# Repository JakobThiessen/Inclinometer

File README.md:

# Inclinometer

- Digital Inclinometer
- Chargetime: 2,5h
- Battery: 250mAh (LiPo)

# Hardware

2 x BMI160

SSD1306

USB --> (VCP) VirtualComPort

# Todo:
## Calibration
## Bootloader over USB

https://github.com/microsoft/uf2

https://github.com/microsoft/uf2-samdx1

# Ab hier nur Beispiel für Markdown-syntax

## Pictures

## Hyperlink

<https://www.markdownguide.org>

<fake@example.com>

<br>

## C++ Example

```cpp
int main() {
  int y = SOME_MACRO_REFERENCE;
  int x = 5 + 6;
  cout << "Hello World! " << x << std::endl();
}
```

## C Example

```c
int main() {
  int y = SOME_MACRO_REFERENCE;
  int x = 5 + 6;
  cout << "Hello World! " << x << std::endl();
}
```

 ## Table
| Column 1      | Column 2     | Column 3     |
| :------------ | :----------- | ------------ |
| Cell Contents | More Stuff   | And Again    |
| You Can Also  | Put Pipes In | Like this \| |

<br>
<br>
<br>

| Column 1   | Column 2   | Column 3                     |
| ---------- | ---------- | ---------------------------- |
| **Things** | _Don't_    | [Need](http://makeuseof.com) |
| To         | *__Look__* | `Pretty`                     |

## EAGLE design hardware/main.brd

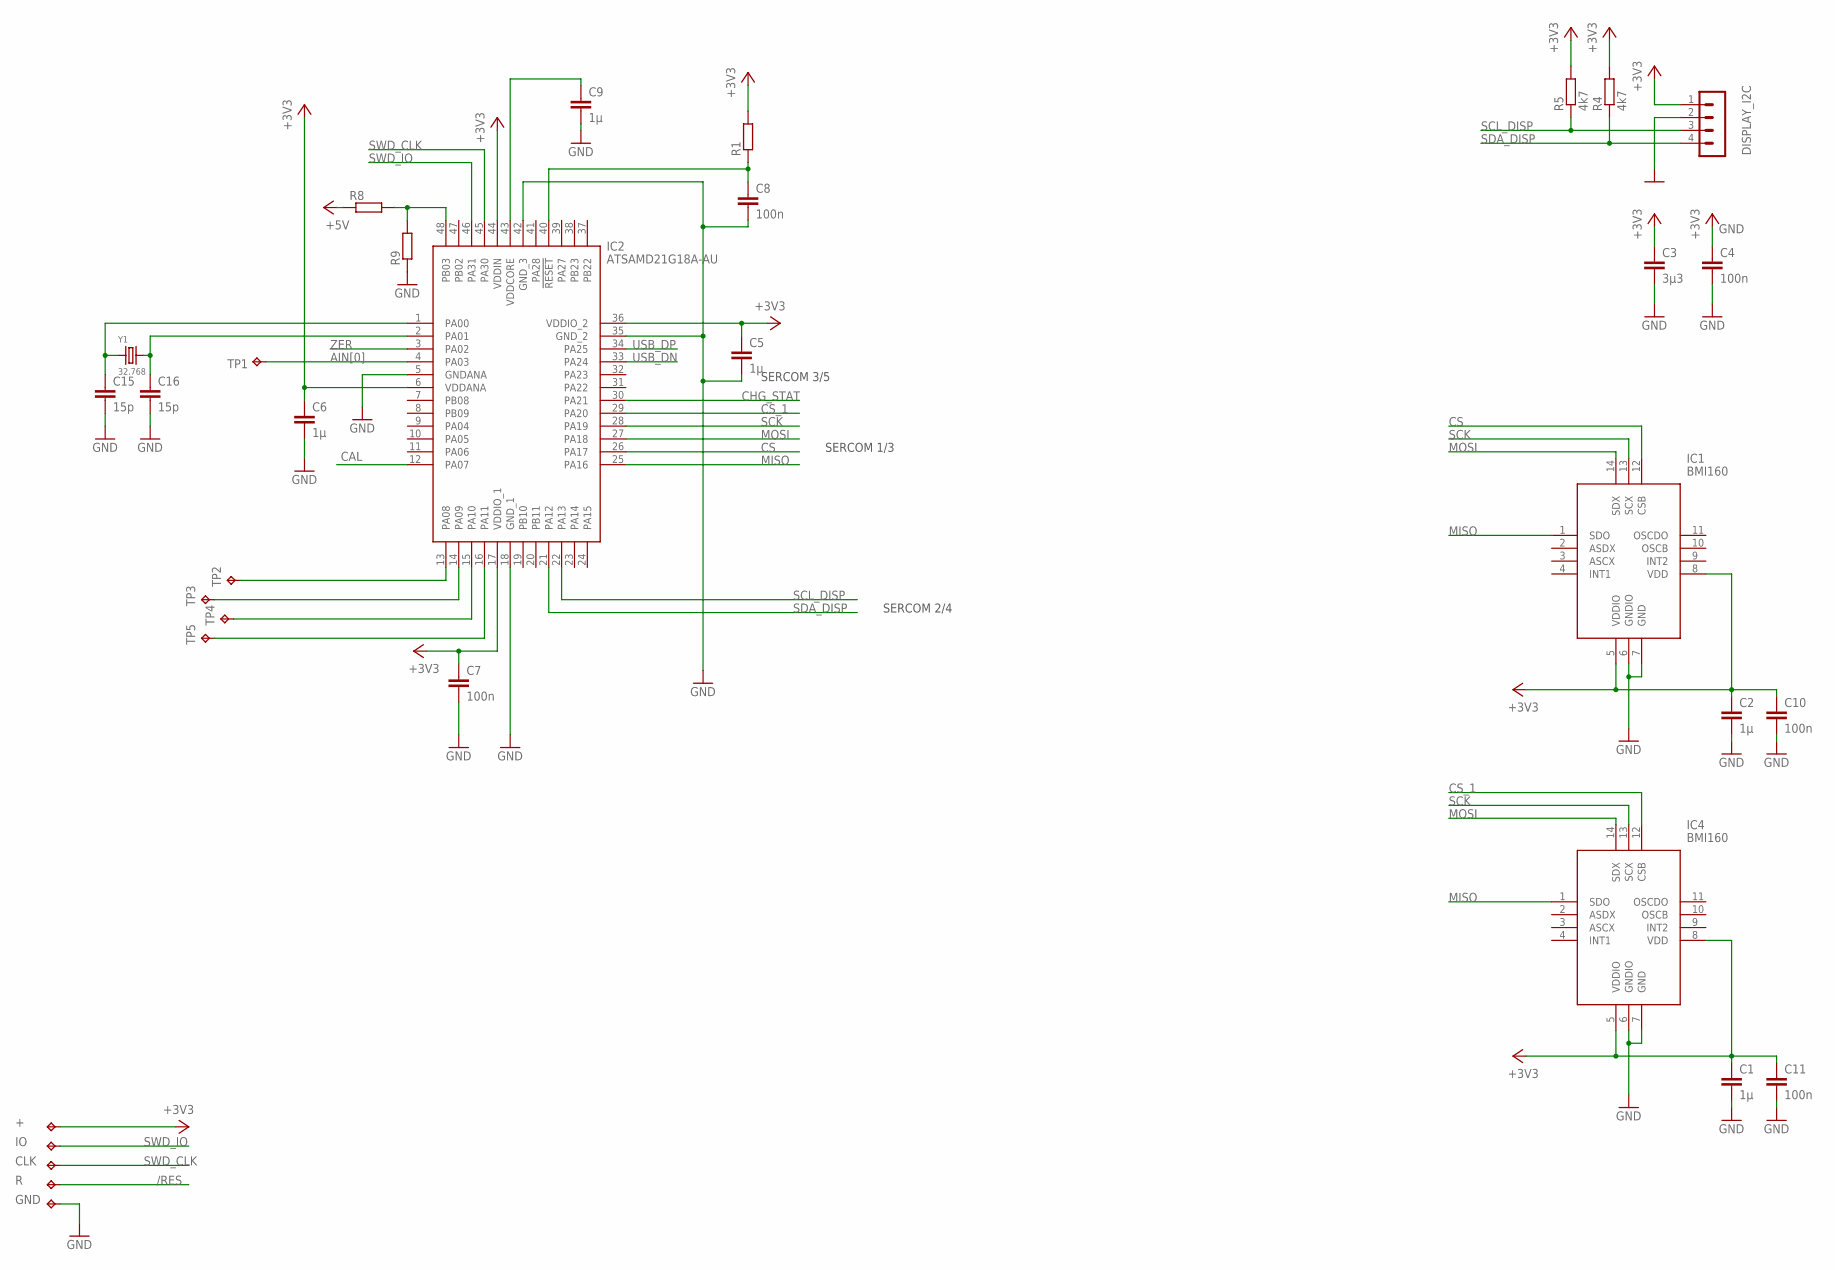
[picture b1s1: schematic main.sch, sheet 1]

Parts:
+: TPB1,27; B1,27
C1, C2, C5, C6, C9: 1µ; C0402K
C3: 3µ3; C0402K
C4, C7, C8, C10, C11: 100n; C0402K
C15, C16: 15p; C0402
CLK: TPB1,27; B1,27
DISPLAY_I2C: MA04-1
GND: TPB1,27; B1,27
IC1, IC4: BMI160; PQFN50P300X250X88-14N
IC2: ATSAMD21G18A-AU; QFP50P900X900X120-48N
IO: TPB1,27; B1,27
R: TPB1,27; B1,27
R1, R8, R9: R-EU_R0402; R0402
R4, R5: 4k7; R0402
TP1, TP2, TP3, TP4, TP5: TPB1,27; B1,27
Y1: 32.768; CRYSTAL_4.9X1.8

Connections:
+3V3: +.TP, C1.1, C2.1, C3.1, C4.1, C5.1, C6.1, C7.1, C10.1, C11.1, DISPLAY_I2C.1, IC1.5 (VDDIO), IC1.8 (VDD), IC2.6 (VDDANA), IC2.17 (VDDIO_1), IC2.36 (VDDIO_2), IC2.44 (VDDIN), IC4.5 (VDDIO), IC4.8 (VDD), R1.2, R4.2, R5.2; also elsewhere on the board
+5V: R8.1; also elsewhere on the board
/RES: C8.1, IC2.40 (!RESET), R.TP, R1.1
AIN[0]: IC2.4 (PA03), TP1.TP
CAL: IC2.12 (PA07); also elsewhere on the board
CHG_STAT: IC2.30 (PA21); also elsewhere on the board
CS: IC1.12 (CSB), IC2.26 (PA17)
CS_1: IC2.29 (PA20), IC4.12 (CSB)
GND: C1.2, C2.2, C3.2, C4.2, C5.2, C6.2, C7.2, C8.2, C9.2, C10.2, C11.2, C15.2, C16.2, DISPLAY_I2C.2, GND.TP, IC1.6 (GNDIO), IC1.7 (GND), IC2.5 (GNDANA), IC2.18 (GND_1), IC2.35 (GND_2), IC2.42 (GND_3), IC4.6 (GNDIO), IC4.7 (GND), R9.1; also elsewhere on the board
MISO: IC1.1 (SDO), IC2.25 (PA16), IC4.1 (SDO)
MOSI: IC1.14 (SDX), IC2.27 (PA18), IC4.14 (SDX)
unnamed: C9.1, IC2.43 (VDDCORE)
unnamed: IC2.13 (PA08), TP2.TP
unnamed: IC2.14 (PA09), TP3.TP
unnamed: IC2.15 (PA10), TP4.TP
unnamed: IC2.16 (PA11), TP5.TP
unnamed: IC2.48 (PB03), R8.2, R9.2
unnamed: C16.1, IC2.2 (PA01), Y1.2
unnamed: C15.1, IC2.1 (PA00), Y1.1
SCK: IC1.13 (SCX), IC2.28 (PA19), IC4.13 (SCX)
SCL_DISP: DISPLAY_I2C.3, IC2.22 (PA13), R5.1
SDA_DISP: DISPLAY_I2C.4, IC2.21 (PA12), R4.1
SWD_CLK: CLK.TP, IC2.45 (PA30)
SWD_IO: IC2.46 (PA31), IO.TP
USB_DN: IC2.33 (PA24); also elsewhere on the board
USB_DP: IC2.34 (PA25); also elsewhere on the board
ZER: IC2.3 (PA02); also elsewhere on the board

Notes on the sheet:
SERCOM 3/5
SERCOM 1/3
SERCOM 2/4

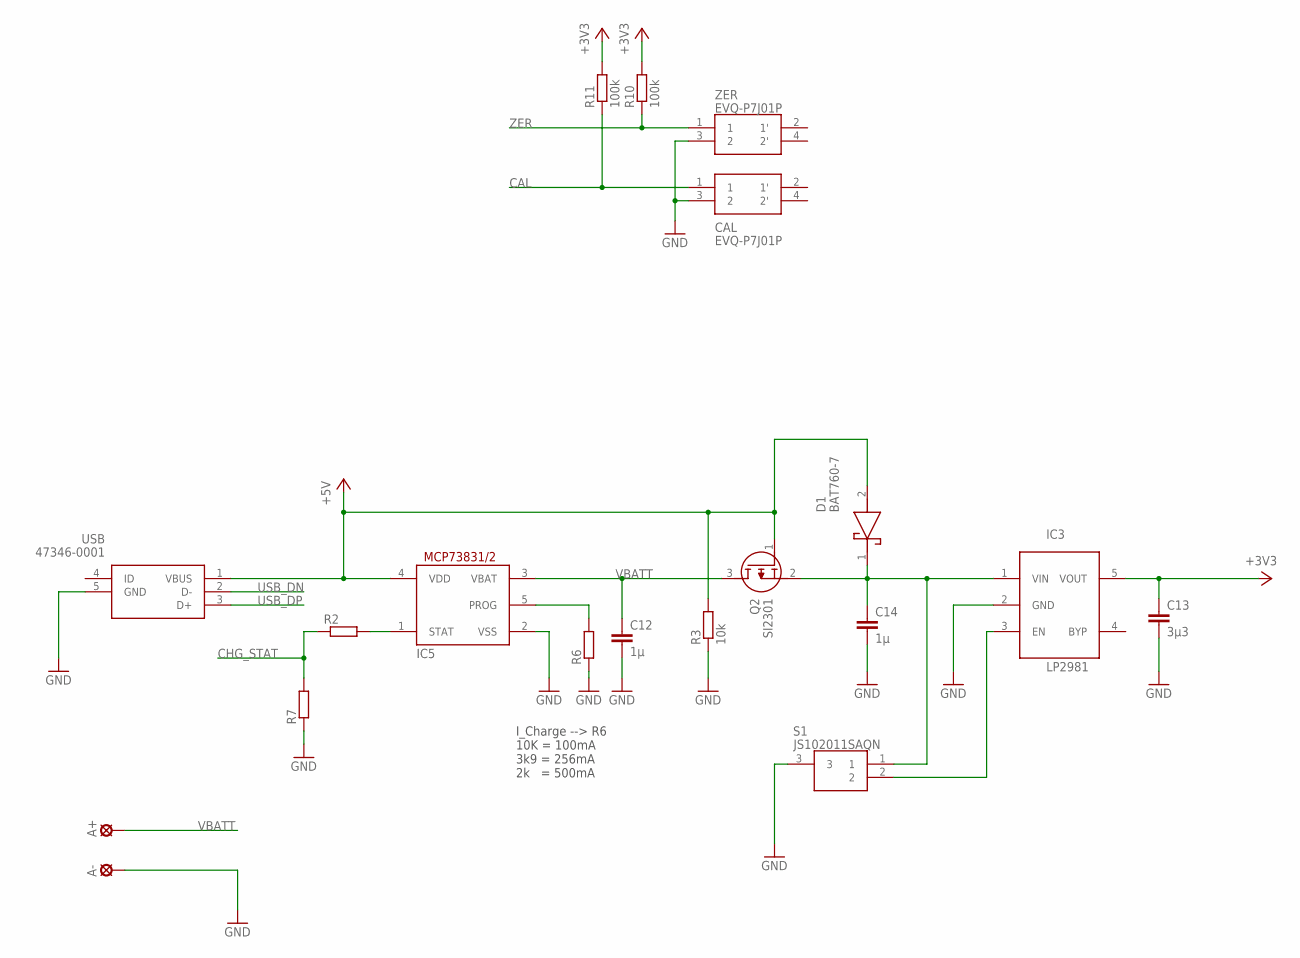
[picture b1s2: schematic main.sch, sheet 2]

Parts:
A+: MCS08
A-: MCS08
C12, C14: 1µ; C0603
C13: 3µ3; C0603
CAL: EVQ-P7J01P; EVQP7J01P
D1: BAT760-7; SOD2513X120N
IC3: LP2981; SOT23-5L
IC5: MCP73831/OT; SOT23-5L
Q2: SI2301; SOT95P240X120-3N
R2, R6, R7: R-EU_R0402; R0402
R3: 10k; R0402
R10, R11: 100k; R0402
S1: JS102011SAQN
USB: 47346-0001
ZER: EVQ-P7J01P; EVQP7J01P

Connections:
+3V3: C13.1, IC3.5 (VOUT), R10.2, R11.2; also elsewhere on the board
+5V: D1.2 (A), IC5.4 (VDD), Q2.1 (G), R3.2, USB.1 (VBUS); also elsewhere on the board
CAL: CAL.1, R11.1; also elsewhere on the board
CHG_STAT: R2.1, R7.2; also elsewhere on the board
GND: A-.MP, C12.2, C13.2, C14.2, CAL.3 (2), IC3.2 (GND), IC5.2 (VSS), R3.1, R6.1, R7.1, S1.3, USB.5 (GND), ZER.3 (2); also elsewhere on the board
unnamed: IC3.3 (EN), S1.2
unnamed: C14.1, D1.1 (K), IC3.1 (VIN), Q2.2 (S), S1.1
unnamed: IC5.1 (STAT), R2.2
unnamed: IC5.5 (PROG), R6.2
USB_DN: USB.2 (D-); also elsewhere on the board
USB_DP: USB.3 (D+); also elsewhere on the board
VBATT: A+.MP, C12.1, IC5.3 (VBAT), Q2.3 (D)
ZER: R10.1, ZER.1; also elsewhere on the board

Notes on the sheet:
I_Charge --> R6 10K = 100mA 3k9 = 256mA 2k = 500mA

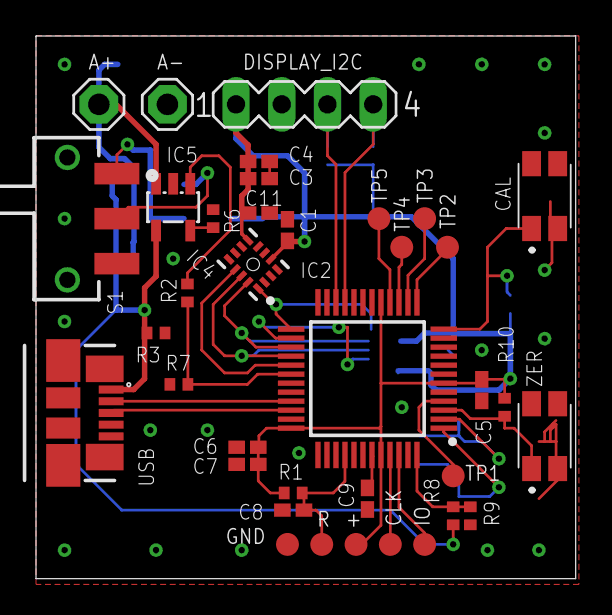
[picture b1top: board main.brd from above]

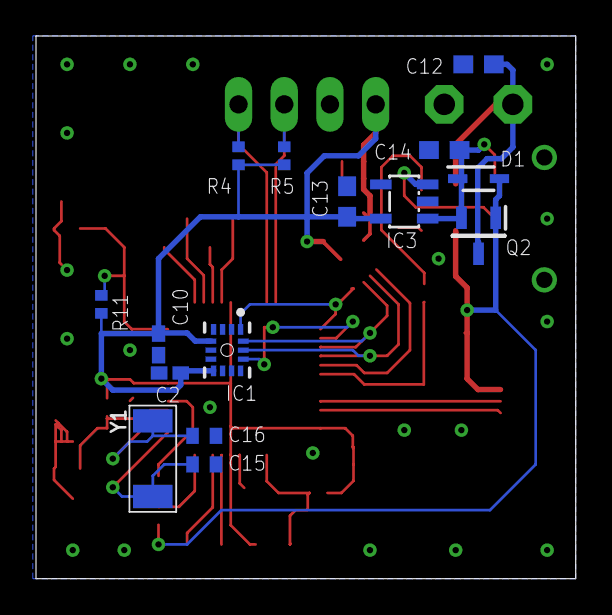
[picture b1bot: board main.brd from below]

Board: 2 copper layers, 30.0 x 30.1 mm, 52 parts (15 on the bottom side), 32 nets.

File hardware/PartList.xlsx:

Qty | vorhanden | Value | Device | Package | Parts | Description | ARROW_PART_NUMBER | ARROW_PRICE-STOCK | HEIGHT | MANUFACTURER_NAME | MANUFACTURER_PART_NUMBER
1 |  |  | MA04-1 | MA04-1 | DISPLAY_I2C | PIN HEADER
6 |  |  | R-EU_R0402 | R0402 | R1, R2, R6, R7, R8, R9 | RESISTOR, European symbol
2 | x | 100k | R-EU_R0402 | R0402 | R10, R11 | RESISTOR, European symbol
5 | x | 100n | C-EUC0402K | C0402K | C4, C7, C8, C10, C11 | CAPACITOR, European symbol
1 | x | 10k | R-EU_R0402 | R0402 | R3 | RESISTOR, European symbol
2 | x | 15p | C-EUC0402 | C0402 | C15, C16 | CAPACITOR, European symbol
5 | x | 1µ | C-EUC0402K | C0402K | C1, C2, C5, C6, C9 | CAPACITOR, European symbol
2 | x | 1µ | C-EUC0603 | C0603 | C12, C14 | CAPACITOR, European symbol
1 | x | 32768 | CRYSTALTHIN32K | CRYSTAL_4.9X1.8 | Y1 | Crystals
1 | x | 3µ3 | C-EUC0402K | C0402K | C3 | CAPACITOR, European symbol
1 | x | 3µ3 | C-EUC0603 | C0603 | C13 | CAPACITOR, European symbol
1 | x | 47346-0001 | 47346-0001 | 47346-0001 | USB | Micro USB B Receptacle Bottom Mount | 47346-0001 |  | mm | Molex | 47346-0001
2 | x | 4k7 | R-EU_R0402 | R0402 | R4, R5 | RESISTOR, European symbol
1 | x | ATSAMD21G18A-AU | ATSAMD21G18A-AU | QFP50P900X900X120-48N | IC2 | ATMEL - ATSAMD21G18A-AU - MCU |  |  | 1.2mm | Microchip | ATSAMD21G18A-AU
1 | x | BAT760-7 | BAT760-7 | SOD2513X120N | D1 | Diode Schottky 30V 1A 2Pin SOD323 Diodes | BAT760-7 | https://www.arrow.com/en/products/bat760-7/diodes-incorporated | 1.2mm | Diodes Inc. | BAT760-7
2 | x | BMI160 | BMI160 | PQFN50P300X250X88-14N | IC1, IC4 | IMUs - Inertial Measurement Units 6-Axis 950uA |  |  | 0.88mm | Bosch Sensortec | BMI160
2 |  | EVQ-P7J01P | EVQ-P7J01P | EVQP7J01P | CAL, ZER | Switch,Tactile,3.5x2.9mm, SPST 50 mA@ 12 V dc 1.7mm | EVQ-P7J01P | https://www.arrow.com/en/products/evq-p7j01p/panasonic | 1mm | Panasonic | EVQ-P7J01P
1 |  | JS102011SAQN | JS102011SAQN | JS102011SAQN | S1 | C & K COMPONENTS - JS102011SAQN - SWITCH, SPDT, 0.6A, 6VDC, SIDE, SMD | JS102011SAQN | https://www.arrow.com/en/products/js102011saqn/ck | mm | C & K COMPONENTS | JS102011SAQN
1 | x | LP2981 | LP298XS | SOT23-5L | IC3
1 |  | MCP73831/OT | MCP73831/OT | SOT23-5L | IC5 | MCP73831/2
1 | x | SI2301 | SI2301 | SOT95P240X120-3N | Q2 | MOSFET P Trench 20V 3A 1V @ 250uA 110 m @ 3A,4.5V SOT23 RoHS | SI2301 |  | 1.2mm | PUOLOP | SI2301

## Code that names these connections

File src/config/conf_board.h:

/**
 * \file
 *
 * \brief User board configuration template
 *
 * Copyright (c) 2013-2018 Microchip Technology Inc. and its subsidiaries.
 *
 * \asf_license_start
 *
 * \page License
 *
 * Subject to your compliance with these terms, you may use Microchip
 * software and any derivatives exclusively with Microchip products.
 * It is your responsibility to comply with third party license terms applicable
 * to your use of third party software (including open source software) that
 * may accompany Microchip software.
 *
 * THIS SOFTWARE IS SUPPLIED BY MICROCHIP "AS IS". NO WARRANTIES,
 * WHETHER EXPRESS, IMPLIED OR STATUTORY, APPLY TO THIS SOFTWARE,
 * INCLUDING ANY IMPLIED WARRANTIES OF NON-INFRINGEMENT, MERCHANTABILITY,
 * AND FITNESS FOR A PARTICULAR PURPOSE. IN NO EVENT WILL MICROCHIP BE
 * LIABLE FOR ANY INDIRECT, SPECIAL, PUNITIVE, INCIDENTAL OR CONSEQUENTIAL
 * LOSS, DAMAGE, COST OR EXPENSE OF ANY KIND WHATSOEVER RELATED TO THE
 * SOFTWARE, HOWEVER CAUSED, EVEN IF MICROCHIP HAS BEEN ADVISED OF THE
 * POSSIBILITY OR THE DAMAGES ARE FORESEEABLE.  TO THE FULLEST EXTENT
 * ALLOWED BY LAW, MICROCHIP'S TOTAL LIABILITY ON ALL CLAIMS IN ANY WAY
 * RELATED TO THIS SOFTWARE WILL NOT EXCEED THE AMOUNT OF FEES, IF ANY,
 * THAT YOU HAVE PAID DIRECTLY TO MICROCHIP FOR THIS SOFTWARE.
 *
 * \asf_license_stop
 *
 */
/*
 * Support and FAQ: visit <a href="https://www.microchip.com/support/">Microchip Support</a>
 */

#ifndef CONF_BOARD_H
#define CONF_BOARD_H

#define CONF_BOARD_USB_VBUS_DETECT

#define SSD1306_I2C_ADDRESS   0x3C
#define SSD1306_128_64

#define BOARD_FREQ_SLCK_XTAL      (32768U)
#define BOARD_FREQ_SLCK_BYPASS    (32768U)
#define BOARD_FREQ_MAINCK_XTAL    0 /* Not Mounted */
#define BOARD_FREQ_MAINCK_BYPASS  0 /* Not Mounted */
#define BOARD_MCK                 CHIP_FREQ_CPU_MAX
#define BOARD_OSC_STARTUP_US      15625

#define	TP_1				PIN_PA03
#define	TP_2				PIN_PA08
#define	TP_3				PIN_PA09
#define	TP_4				PIN_PA10
#define	TP_5				PIN_PA11

#define ANALOG_0_PIN		TP_1
#define USB_VOLTAGE_PIN		PIN_PB03

#define CHARGE_STATUS		PIN_PA21

#define SW0_PIN				PIN_PA07
#define BUTTON_0_NAME       "CAL"
#define BUTTON_0_PIN        SW0_PIN
#define BUTTON_0_ACTIVE     false
#define BUTTON_0_INACTIVE   true
#define BUTTON_0_EIC_PIN    PIN_PA07A_EIC_EXTINT7
#define BUTTON_0_EIC_MUX    MUX_PA07A_EIC_EXTINT7
#define BUTTON_0_EIC_PINMUX	PINMUX_PA07A_EIC_EXTINT7
#define BUTTON_0_EIC_LINE   7

#define SW1_PIN				PIN_PA02
#define BUTTON_1_NAME       "ZER"
#define BUTTON_1_PIN        SW1_PIN
#define BUTTON_1_ACTIVE     false
#define BUTTON_1_INACTIVE   true
#define BUTTON_1_EIC_PIN    PIN_PA02A_EIC_EXTINT2
#define BUTTON_1_EIC_MUX    MUX_PA02A_EIC_EXTINT2
#define BUTTON_1_EIC_PINMUX	PINMUX_PA02A_EIC_EXTINT2
#define BUTTON_1_EIC_LINE   7

// SPI SENSOR (SERCOM 1/3)
#define SENSOR_SPI_SS_1     PIN_PA20
#define SENSOR_SPI_SS_0     PIN_PA17

#define SENSOR_SPI_SCK		PIN_PA19
#define SENSOR_SPI_MOSI		PIN_PA18
#define SENSOR_SPI_MISO		PIN_PA16

#define SENSOR_SERCOM		SERCOM1

#define CONF_MASTER_MUX_SETTING	SPI_SIGNAL_MUX_SETTING_E
#define CONF_MASTER_PINMUX_PAD0 PINMUX_PA16C_SERCOM1_PAD0
#define CONF_MASTER_PINMUX_PAD1	PINMUX_UNUSED
#define CONF_MASTER_PINMUX_PAD2 PINMUX_PA18C_SERCOM1_PAD2
#define CONF_MASTER_PINMUX_PAD3	PINMUX_PA19C_SERCOM1_PAD3

//I²C DISPLAY (SERCOM 2/4)
#define DOSPLAY_SERCOM		SERCOM2

#define SCL_DISP_PIN		PIN_PA13
#define SDA_DISP_PIN		PIN_PA12

#define DISPLAY_I2C_SERCOM_PINMUX_PAD0  PINMUX_PA12C_SERCOM2_PAD0
#define DISPLAY_I2C_SERCOM_PINMUX_PAD1  PINMUX_PA13C_SERCOM2_PAD1

#endif // CONF_BOARD_H

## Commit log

2020-09-04 initial version
2020-09-04 Änderung
2020-09-04 test
2020-09-10 Update main.c
    add drawOuterFrame() Funktion
    Ab einem bestimmten Winkwl wird das Display um 180° gedreht.
2020-09-10 Funktion SSD1306_FlipHorizontalDisplay() hinzugefügt

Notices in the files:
parts and their libraries:
microbuilder: This work is placed in the public domain, and may be freely used for commercial and non-commercial work with the following conditions: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
